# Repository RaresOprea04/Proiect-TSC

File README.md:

# InkTime - Open Source Smartwatch ⌚

InkTime este un start-up care își propune să creeze un smartwatch accesibil și complet open-source. Acest repository conține fișierele FINALE, inclusiv design-ul hardware (schematic + PCB 2D/3D în Fusion 360), fișierele de fabricație și documentația aferentă, cât și ceas-ul în forma sa finală, asamblat.

## 1. Diagrama Bloc a Sistemului

Diagrama de mai jos ilustrează arhitectura hardware a ceasului InkTime, având în centru procesorul nRF52840, înconjurat de modulele de power management, senzori și interfața cu utilizatorul.

```mermaid
flowchart LR
    %% Stiluri
    classDef power fill:#f9d0c4,stroke:#333,stroke-width:2px;
    classDef mcu fill:#d4e6f1,stroke:#333,stroke-width:2px;
    classDef peri fill:#d5f5e3,stroke:#333,stroke-width:2px;

    %% Power Block
    subgraph Power Management
        USB[Conector USB-C]:::power -->|VBUS 5V| BQ[BQ25180\nCharger Li-Po]:::power
        BAT[(Baterie Li-Po)]:::power <-->|VBAT| BQ
        BQ -->|VSYS| REG[RT6160\nRegulator 3.3V]:::power
    end

    %% MCU Block
    MCU{nRF52840 SoC\nMCU + Antenă BLE}:::mcu

    %% Peripherals
    subgraph Senzori & UI
        ACC[BMA421\nAccelerometru]:::peri
        BTN[Butoane Tactile]:::peri
    end

    subgraph Output
        EPD[Ecran E-Paper]:::peri
    end

    Debug[Interfață SWD\nProgramare]:::peri

    %% Power Connections (Linii groase)
    REG == 3.3V === MCU
    REG == 3.3V === ACC
    REG == 3.3V === EPD

    %% Data Connections (Linii normale)
    MCU <-->|I2C| ACC
    MCU -->|SPI| EPD
    BTN -->|GPIO| MCU
    MCU <-->|SWDIO / SWCLK| Debug
```

## 2. Bill of Materials (BOM)

Toate componentele pasive (rezistențe, condensatoare) sunt în format SMD 0201 sau 0402, conform specificațiilor proiectului. Mai jos sunt componentele integrate principale (IC-urile):

| Componentă / Modul | Rol | JLCPCB Part Link | Datasheet |
| :--- | :--- | :--- | :--- |
| **nRF52840-QIAA** | MCU principal (Bluetooth LE) | [Caută JLC](https://jlcpcb.com/parts) | [Datasheet nRF52840](https://infocenter.nordicsemi.com/pdf/nRF52840_PS_v1.1.pdf) |
| **BQ25180YBGR** | PMIC / LiPo Battery Charger | [Caută JLC](https://jlcpcb.com/parts) | [Datasheet BQ25180](https://www.ti.com/lit/ds/symlink/bq25180.pdf) |
| **RT6160AWSC** | DC/DC Buck-Boost Converter (3.3V) | [Caută JLC](https://jlcpcb.com/parts) | [Datasheet RT6160](https://www.richtek.com/assets/product_file/RT6160A/DS6160A-01.pdf) |
| **MAX17048G+T10** | Fuel Gauge (Monitorizare Baterie) | [Caută JLC](https://jlcpcb.com/parts) | [Datasheet MAX17048](https://datasheets.maximintegrated.com/en/ds/MAX17048-MAX17049.pdf) |
| **BMA421** | Senzor IMU (Accelerometru) | [Caută JLC](https://jlcpcb.com/parts) | [Datasheet BMA421](https://www.bosch-sensortec.com/media/boschsensortec/downloads/datasheets/bst-bma421-fl000.pdf) |
| **DRV2605YZFR** | Haptic Motor Driver | [Caută JLC](https://jlcpcb.com/parts) | [Datasheet DRV2605](https://www.ti.com/lit/ds/symlink/drv2605.pdf) |
| **E-Paper Display** | Conector Display FPC 24-pin | - | - |

---

## 3. Funcționalitate Hardware și Arhitectură

Sistemul este construit în jurul microcontroller-ului **Nordic nRF52840**, ales pentru eficiența energetică ridicată și capabilitățile native Bluetooth Low Energy (BLE). 

### Alimentare (Power Management)
* **Încărcare:** Sistemul folosește un încărcător liniar **BQ25180** compatibil cu baterii LiPo, alimentat prin mufa USB-C (5V). 
* **Regulare:** Deoarece bateria variază între 3.0V și 4.2V, folosim un convertor DC/DC Buck-Boost **RT6160** pentru a menține o tensiune stabilă de 3.3V necesară componentelor logice și display-ului.
* **Monitorizare:** Modulul **MAX17048** comunică prin I2C pentru a oferi SoC-ului informații exacte despre procentajul bateriei (State of Charge).

### Senzori și Interacțiune
* **Membru senzorial:** Un IMU **BMA421** comunică prin I2C cu microcontroller-ul. Folosește pini de interupt pentru a trezi procesorul (Wake-on-Motion), economisind astfel energie (ex: se aprinde display-ul doar când ridici mâna).
* **Display E-Paper:** Este controlat printr-o magistrală SPI (MISO, MOSI, SCK, CS) la care se adaugă semnalele de control specifice ecranelor cu cerneală electronică (BUSY, DC, RESET). Avantajul suprem este că ecranul reține imaginea fără a consuma energie (0mA consum static).
* **Feedback Haptic:** Un driver dedicat **DRV2605** este conectat pe magistrala I2C și controlează un motor de vibrații (shaker) pentru notificări.
* **Input Utilizator:** 3 butoane fizice cu rezistențe de pull-up hardware/software pentru navigarea în meniu.

### Estimări de consum energetic
* **Sleep Mode (System OFF):** ~1.5uA (nRF52840) + curenții de stand-by ai senzorilor = **< 5uA total**.
* **Display Refresh:** ~8mA timp de 1-2 secunde (doar la actualizarea orei).
* **BLE Tx/Rx Active:** ~5.3mA pe vârfuri scurte (câteva milisecunde).
Sistemul este extrem de eficient, asigurând o durată de viață a bateriei de câteva săptămâni, în funcție de frecvența refresh-urilor e-paper.

---

## 4. Maparea Pinilor nRF52840 (Pinout)

| Pin nRF52840 | Nume Semnal | Destinație | Rol / Explicație |
| :--- | :--- | :--- | :--- |
| `P0.06` | I2C_SDA | BMA421, BQ25180, MAX17048, DRV2605 | Linia de date pentru magistrala I2C comună. |
| `P0.07` | I2C_SCL | BMA421, BQ25180, MAX17048, DRV2605 | Linia de clock pentru magistrala I2C comună. |
| `P0.03` | SPI_MOSI | E-Paper Connector | Trimite comenzi și date de imagine către display. |
| `P0.02` | SPI_SCK | E-Paper Connector | Semnalul de clock pentru interfața SPI a display-ului. |
| `P0.05` | EPD_CS | E-Paper Connector | Chip Select (active low) pentru display-ul E-paper. |
| `P0.15` | EPD_DC | E-Paper Connector | Data/Command - indică dacă payload-ul trimis prin SPI este o comandă sau date de pixel. |
| `P0.17` | EPD_BUSY | E-Paper Connector | Citește starea de busy a display-ului pentru a ști când s-a terminat refresh-ul. |
| `P0.16` | EPD_RST | E-Paper Connector | Pinul de hardware reset pentru ecranul E-paper. |
| `P0.08` | IMU_INT1 | BMA421 | Wake-up interrupt (ex: trezirea sistemului la ridicarea mâinii). |
| `P1.04` | SW_UP | Buton Sus | Input navigație (activ low, folosind pull-up intern). |
| `P1.05` | SW_ENT | Buton Enter | Input navigație (activ low, folosind pull-up intern). |
| `P1.06` | SW_DN | Buton Jos | Input navigație (activ low, folosind pull-up intern). |

---

## 5. Design Log & Constrângeri pentru Review

### Imagini PCB și Asamblare 3D
*Aici puteți vedea design-ul plăcii de circuit și integrarea acesteia în carcasa printată.*

**Vedere PCB (Top & Bottom):**

**Integrare în Carcasă (Asamblare internă):**

### Jurnal de decizii (Design Log)
În timpul procesului de proiectare am respectat următoarele constrângeri și decizii de good-practice:
1. **Plane de Masă:** S-au implementat poligoane de GND atât pe layer-ul TOP cât și pe BOTTOM. S-a realizat Via Stitching abundent pentru a asigura un plan de referință solid, în special în apropierea modulului radio și a convertoarelor DC/DC.
2. **Zona Antenei:** Am respectat cu strictețe zona de clearance pentru antena integrată. S-a folosit un "Polygon Cutout" pe ambele straturi pentru a decupa cuprul complet de sub antenă, evitând astfel detunarea (detuning) acesteia și degradarea semnalului RF.
3. **Rutarea curentului:** Traseele de putere (VBUS, 3V3, VBAT) au fost rutate la o grosime optimizată de 0.3mm (unde spațiul a permis) pentru a minimiza căderea de tensiune, iar condensatoarele de decuplare (100nF) au fost amplasate strict, cât mai aproape de pinii de VDD ai integratelor.
4. **Acceptare Erori DRC:** Erorile de clearance și dimension rezultate din depășirea marginii plăcii de către componentele mecanice (mufa USB-C și butoanele fizice) au fost acceptate asumat, deoarece amplasarea lor este impusă de cotele carcasei exterioare.

---

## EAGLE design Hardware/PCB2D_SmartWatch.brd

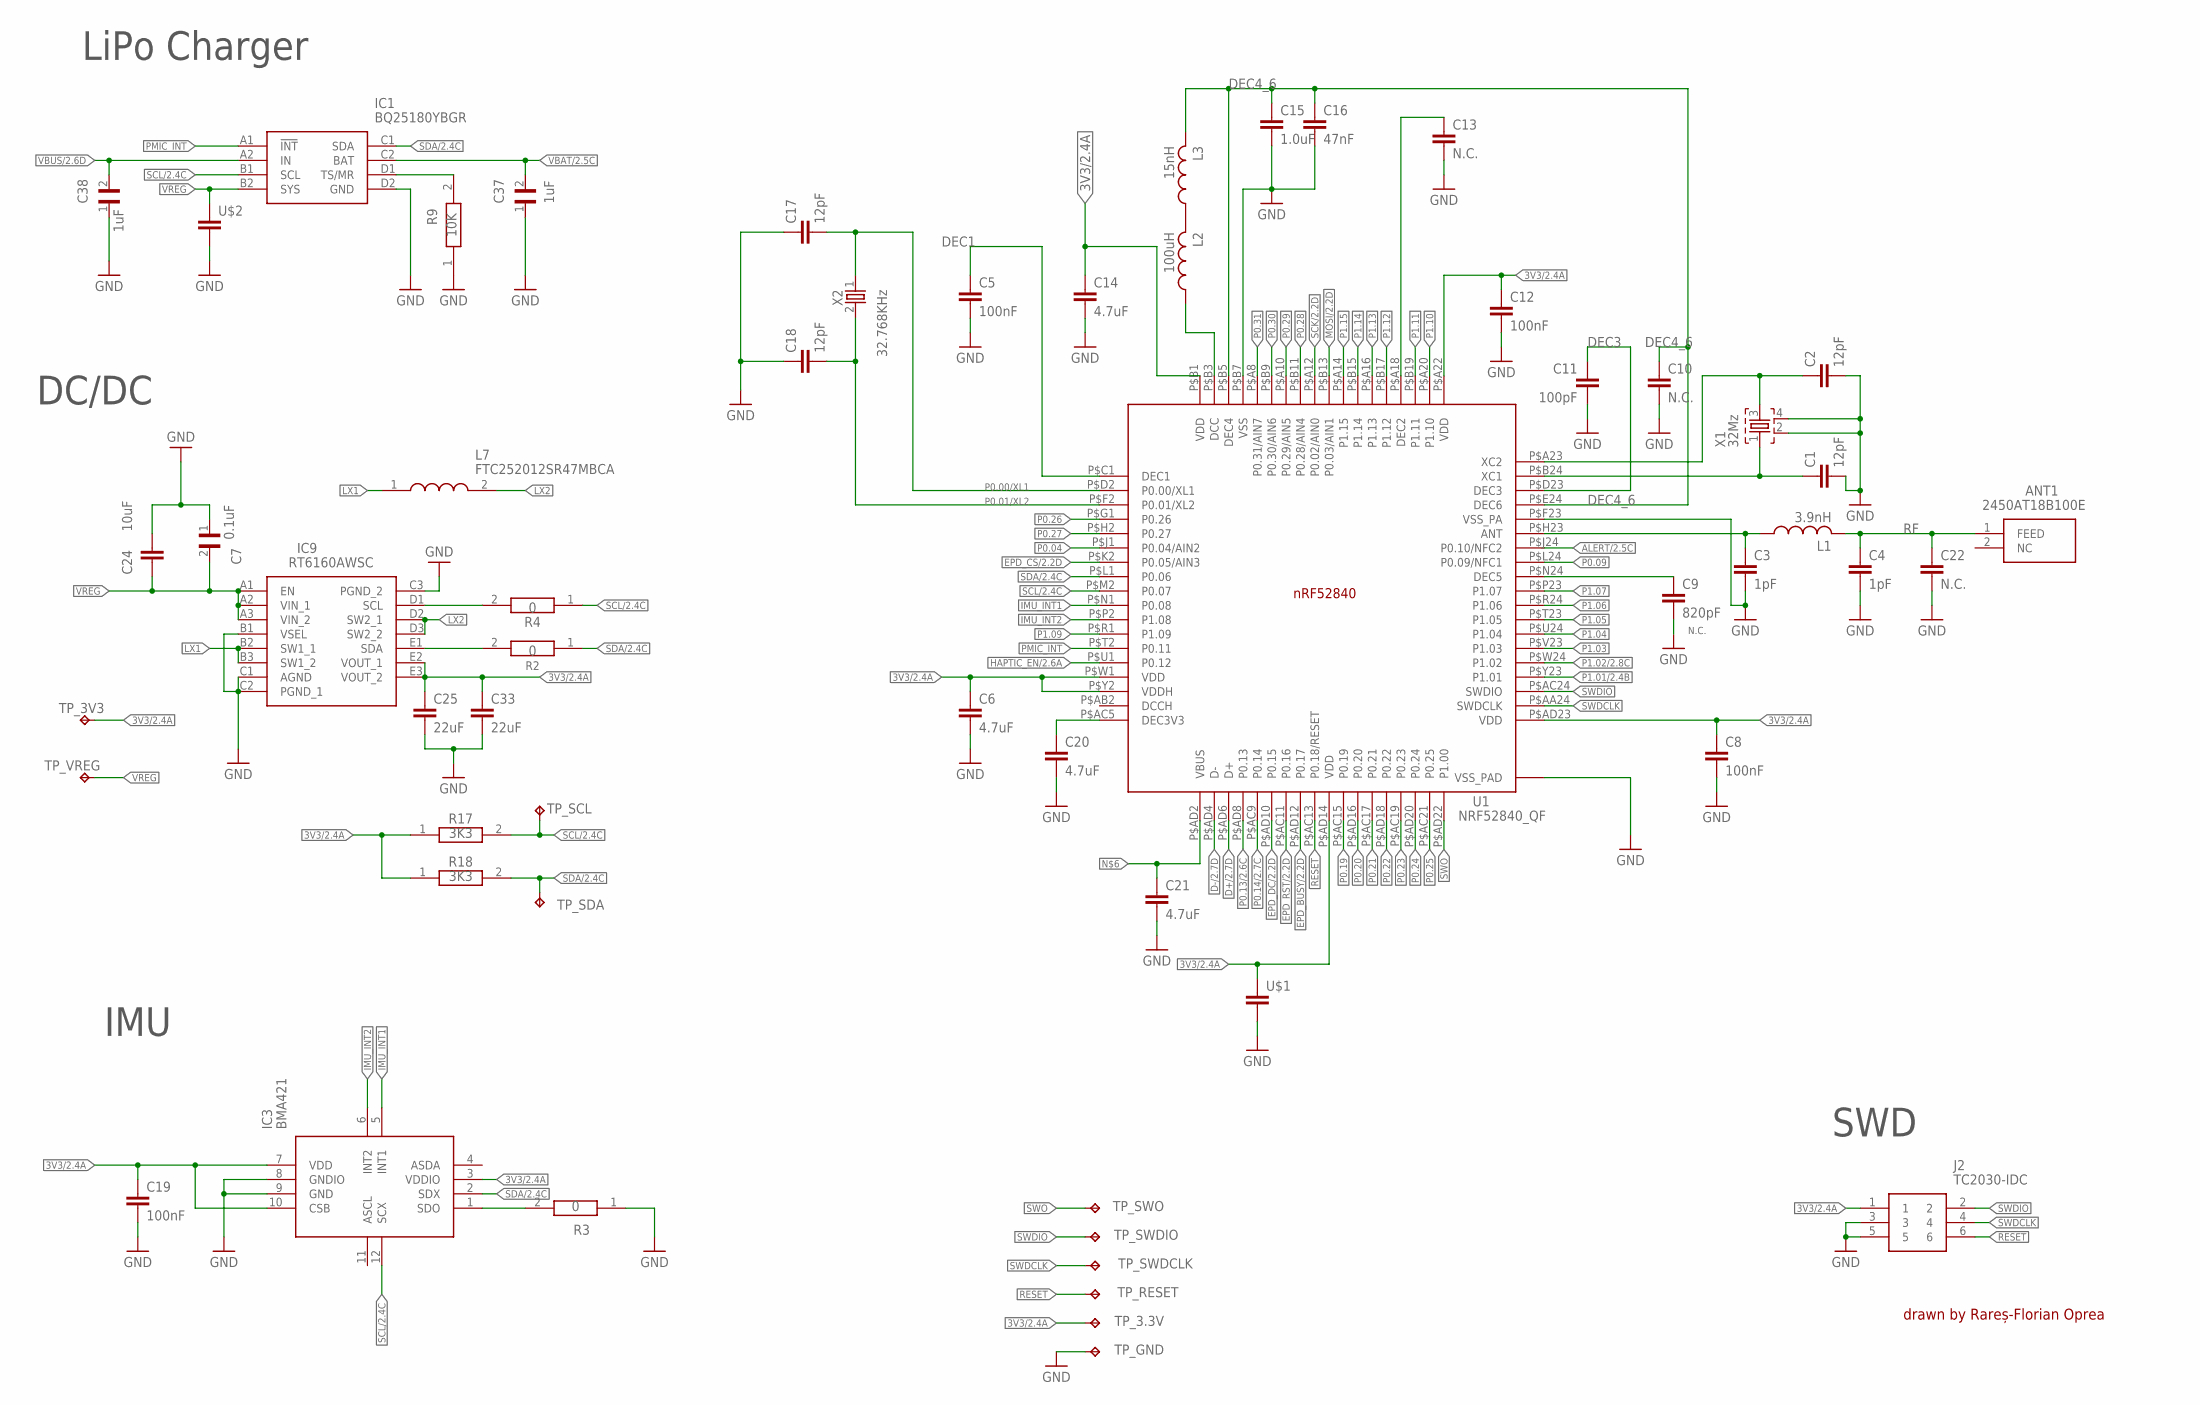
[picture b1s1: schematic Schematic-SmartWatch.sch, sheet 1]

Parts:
ANT1: 2450AT18B100E; 2450AT18B100E_ANTC3216X140N
C1, C2, C17, C18: 12pF; NORDIC_NRF_3_RESC0201_L
C3, C4: 1pF; NORDIC_NRF_3_RESC0201_L
C5, C8, C12, C19: 100nF; NORDIC_NRF_3_RESC0201_L
C6, C14, C20, C21: 4.7uF; NORDIC_NRF_3_RESC0201_L
C7: 0.1uF; GRM011R60J152KE01L_2_CAPC0201X13N
C9: 820pF; NORDIC_NRF_3_RESC0201_L
C10, C13, C22: N.C.; NORDIC_NRF_3_RESC0201_L
C11: 100pF; NORDIC_NRF_3_RESC0201_L
C15: 1.0uF; NORDIC_NRF_3_RESC0201_L
C16: 47nF; NORDIC_NRF_3_RESC0201_L
C24: 10uF; NORDIC_NRF_3_RESC0201_L
C25, C33: 22uF; NORDIC_NRF_3_RESC0201_L
C37: 1uF; GRM011R60J152KE01L_1_0201
C38: 1uF; GRM011R60J152KE01L_2_CAPC0201X13N
IC1: BQ25180YBGR; BQ25180YBGR_BGA8C40P2X4_100X155X50
IC3: BMA421; BMA423_BMA423
IC9: RT6160AWSC; RT6160AWSC_BGA15C40P3X5_140X230X60
J2: TC2030-IDC; TC2030-IDC_TC2030IDC
L1: 3.9nH; NORDIC_NRF_2_RESC0402_L
L2: 100uH; NORDIC_NRF_2_RESC0402_L
L3: 15nH; NORDIC_NRF_2_RESC0402_L
L7: FTC252012SR47MBCA; MLP2016SR47MT0S1_INDC2016X100N
R2, R4: 0; CPF0201D7K68C1_0201
R3: 0; ERA-1AEB3401C_0201
R9: 10K; ERA-1AEB3401C_0201
R17, R18: 3K3; CPF0201D7K68C1_0201
TP_3.3V, TP_3V3: HECTOR_WATCH_1_TPTP20R; HECTOR_WATCH_1_TP20R
TP_GND: HECTOR_WATCH_1_TPTP20R; HECTOR_WATCH_1_TP20R
TP_RESET: HECTOR_WATCH_1_TPTP20R; HECTOR_WATCH_1_TP20R
TP_SCL: HECTOR_WATCH_1_TPTP20R; HECTOR_WATCH_1_TP20R
TP_SDA: HECTOR_WATCH_1_TPTP20R; HECTOR_WATCH_1_TP20R
TP_SWDCLK: HECTOR_WATCH_1_TPTP20R; HECTOR_WATCH_1_TP20R
TP_SWDIO: HECTOR_WATCH_1_TPTP20R; HECTOR_WATCH_1_TP20R
TP_SWO: HECTOR_WATCH_1_TPTP20R; HECTOR_WATCH_1_TP20R
TP_VREG: HECTOR_WATCH_1_TPTP20R; HECTOR_WATCH_1_TP20R
U1: NRF52840_QF; NORDIC_NRF_4_AQFN50P700X700X85_HS-74N
U$1, U$2: NORDIC_NRF_3_CAPACITOR_0201_L; NORDIC_NRF_3_RESC0201_L
X1: 32Mz; NORDIC_NRF_BT-XTAL_2016_N
X2: 32.768KHz; NORDIC_NRF_1_XTAL_3215_N

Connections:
3V3/2.4A: C6.1, C8.1, C12.1, C14.1, C19.1, C25.1, C33.1, IC3.3 (VDDIO), IC3.7 (VDD), IC3.10 (CSB), IC9.E2 (VOUT_1), IC9.E3 (VOUT_2), J2.1, R17.1, R18.1, TP_3.3V.TP, TP_3V3.TP, U1.P$A22 (VDD), U1.P$AD14 (VDD), U1.P$AD23 (VDD), U1.P$B1 (VDD), U1.P$W1 (VDD), U1.P$Y2 (VDDH), U$1.1
ALERT/2.5C: U1.P$J24 (P0.10/NFC2)
D+/2.7D: U1.P$AD6 (D+)
D-/2.7D: U1.P$AD4 (D-)
DEC1: C5.1, U1.P$C1 (DEC1)
DEC3: C11.1, U1.P$D23 (DEC3)
DEC4_6: C10.1, C15.1, C16.1, L3.2, U1.P$B5 (DEC4), U1.P$E24 (DEC6)
EPD_BUSY/2.2D: U1.P$AD12 (P0.17)
EPD_CS/2.2D: U1.P$K2 (P0.05/AIN3)
EPD_DC/2.2D: U1.P$AD10 (P0.15)
EPD_RST/2.2D: U1.P$AC11 (P0.16)
GND: C1.2, C2.2, C3.2, C4.2, C5.2, C6.2, C7.1, C8.2, C10.2, C11.2, C12.2, C13.2, C14.2, C19.2, C20.2, C21.2, C22.2, C24.1, C37.1, C38.1, IC1.D2 (GND), IC3.8 (GNDIO), IC3.9 (GND), IC9.B1 (VSEL), IC9.C1 (AGND), IC9.C2 (PGND_1), J2.3, J2.5, R3.1, R9.1, TP_GND.TP, U1.P$74 (VSS_PAD), U1.P$75 (VSS_PAD), U1.P$76 (VSS_PAD), U1.P$77 (VSS_PAD), U1.P$78 (VSS_PAD), U1.P$79 (VSS_PAD), U1.P$80 (VSS_PAD), U1.P$81 (VSS_PAD), U1.P$82 (VSS_PAD), U1.P$83 (VSS_PAD), U1.P$84 (VSS_PAD), U1.P$85 (VSS_PAD), U1.P$86 (VSS_PAD), U1.P$87 (VSS_PAD), U1.P$88 (VSS_PAD), U1.P$89 (VSS_PAD), U1.P$90 (VSS_PAD), U1.P$F23 (VSS_PA), U$1.2, U$2.2, X1.2, X1.4; also elsewhere on the board
HAPTIC_EN/2.6A: U1.P$U1 (P0.12)
IMU_INT1: IC3.5 (INT1), U1.P$N1 (P0.08)
IMU_INT2: IC3.6 (INT2), U1.P$P2 (P1.08)
LX1: IC9.B2 (SW1_1), IC9.B3 (SW1_2), L7.1
LX2: IC9.D2 (SW2_1), IC9.D3 (SW2_2), L7.2
MOSI/2.2D: U1.P$B13 (P0.03/AIN1)
unnamed: L2.2, L3.1
unnamed: L2.1, U1.P$B3 (DCC)
unnamed: IC1.D1 (TS/MR), R9.2
unnamed: C15.2, C16.2, U1.P$B7 (VSS)
unnamed: C20.1, U1.P$AC5 (DEC3V3)
unnamed: C21.1, U1.P$AD2 (VBUS)
unnamed: C17.1, C18.1
unnamed: C3.1, L1.1, U1.P$H23 (ANT)
unnamed: C1.1, U1.P$B24 (XC1), X1.1
unnamed: C13.1, U1.P$A18 (DEC2)
unnamed: C9.1, U1.P$N24 (DEC5)
unnamed: C2.1, U1.P$A23 (XC2), X1.3
unnamed: IC3.1 (SDO), R3.2
unnamed: IC9.D1 (SCL), R4.2
unnamed: C25.2, C33.2
unnamed: IC9.E1 (SDA), R2.2
N.C.: C9.2
P0.00/XL1: C17.2, U1.P$D2 (P0.00/XL1), X2.1
P0.01/XL2: C18.2, U1.P$F2 (P0.01/XL2), X2.2
P0.04: U1.P$J1 (P0.04/AIN2)
P0.09: U1.P$L24 (P0.09/NFC1)
P0.13/2.6C: U1.P$AD8 (P0.13)
P0.14/2.7C: U1.P$AC9 (P0.14)
P0.19: U1.P$AC15 (P0.19)
P0.20: U1.P$AD16 (P0.20)
P0.21: U1.P$AC17 (P0.21)
P0.22: U1.P$AD18 (P0.22)
P0.23: U1.P$AC19 (P0.23)
P0.24: U1.P$AD20 (P0.24)
P0.25: U1.P$AC21 (P0.25)
P0.26: U1.P$G1 (P0.26)
P0.27: U1.P$H2 (P0.27)
P0.28: U1.P$B11 (P0.28/AIN4)
P0.29: U1.P$A10 (P0.29/AIN5)
P0.30: U1.P$B9 (P0.30/AIN6)
P0.31: U1.P$A8 (P0.31/AIN7)
P1.01/2.4B: U1.P$Y23 (P1.01)
P1.02/2.8C: U1.P$W24 (P1.02)
P1.03: U1.P$V23 (P1.03)
P1.04: U1.P$U24 (P1.04)
P1.05: U1.P$T23 (P1.05)
P1.06: U1.P$R24 (P1.06)
P1.07: U1.P$P23 (P1.07)
P1.09: U1.P$R1 (P1.09)
P1.10: U1.P$A20 (P1.10)
P1.11: U1.P$B19 (P1.11)
P1.12: U1.P$B17 (P1.12)
P1.13: U1.P$A16 (P1.13)
P1.14: U1.P$B15 (P1.14)
P1.15: U1.P$A14 (P1.15)
PMIC_INT: IC1.A1 (!INT), U1.P$T2 (P0.11)
RESET: J2.6, TP_RESET.TP, U1.P$AC13 (P0.18/RESET)
RF: ANT1.1 (FEED), C4.1, C22.1, L1.2
SCK/2.2D: U1.P$A12 (P0.02/AIN0)
SCL/2.4C: IC1.B1 (SCL), IC3.12 (SCX), R4.1, R17.2, TP_SCL.TP, U1.P$M2 (P0.07)
SDA/2.4C: IC1.C1 (SDA), IC3.2 (SDX), R2.1, R18.2, TP_SDA.TP, U1.P$L1 (P0.06)
SWDCLK: J2.4, TP_SWDCLK.TP, U1.P$AA24 (SWDCLK)
SWDIO: J2.2, TP_SWDIO.TP, U1.P$AC24 (SWDIO)
SWO: TP_SWO.TP, U1.P$AD22 (P1.00)
VBAT/2.5C: C37.2, IC1.C2 (BAT)
VBUS/2.6D: C38.2, IC1.A2 (IN)
VREG: C7.2, C24.2, IC1.B2 (SYS), IC9.A1 (EN), IC9.A2 (VIN_1), IC9.A3 (VIN_2), TP_VREG.TP, U$2.1

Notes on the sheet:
LiPo Charger
IMU
DC/DC
SWD
drawn by Rareș-Florian Oprea

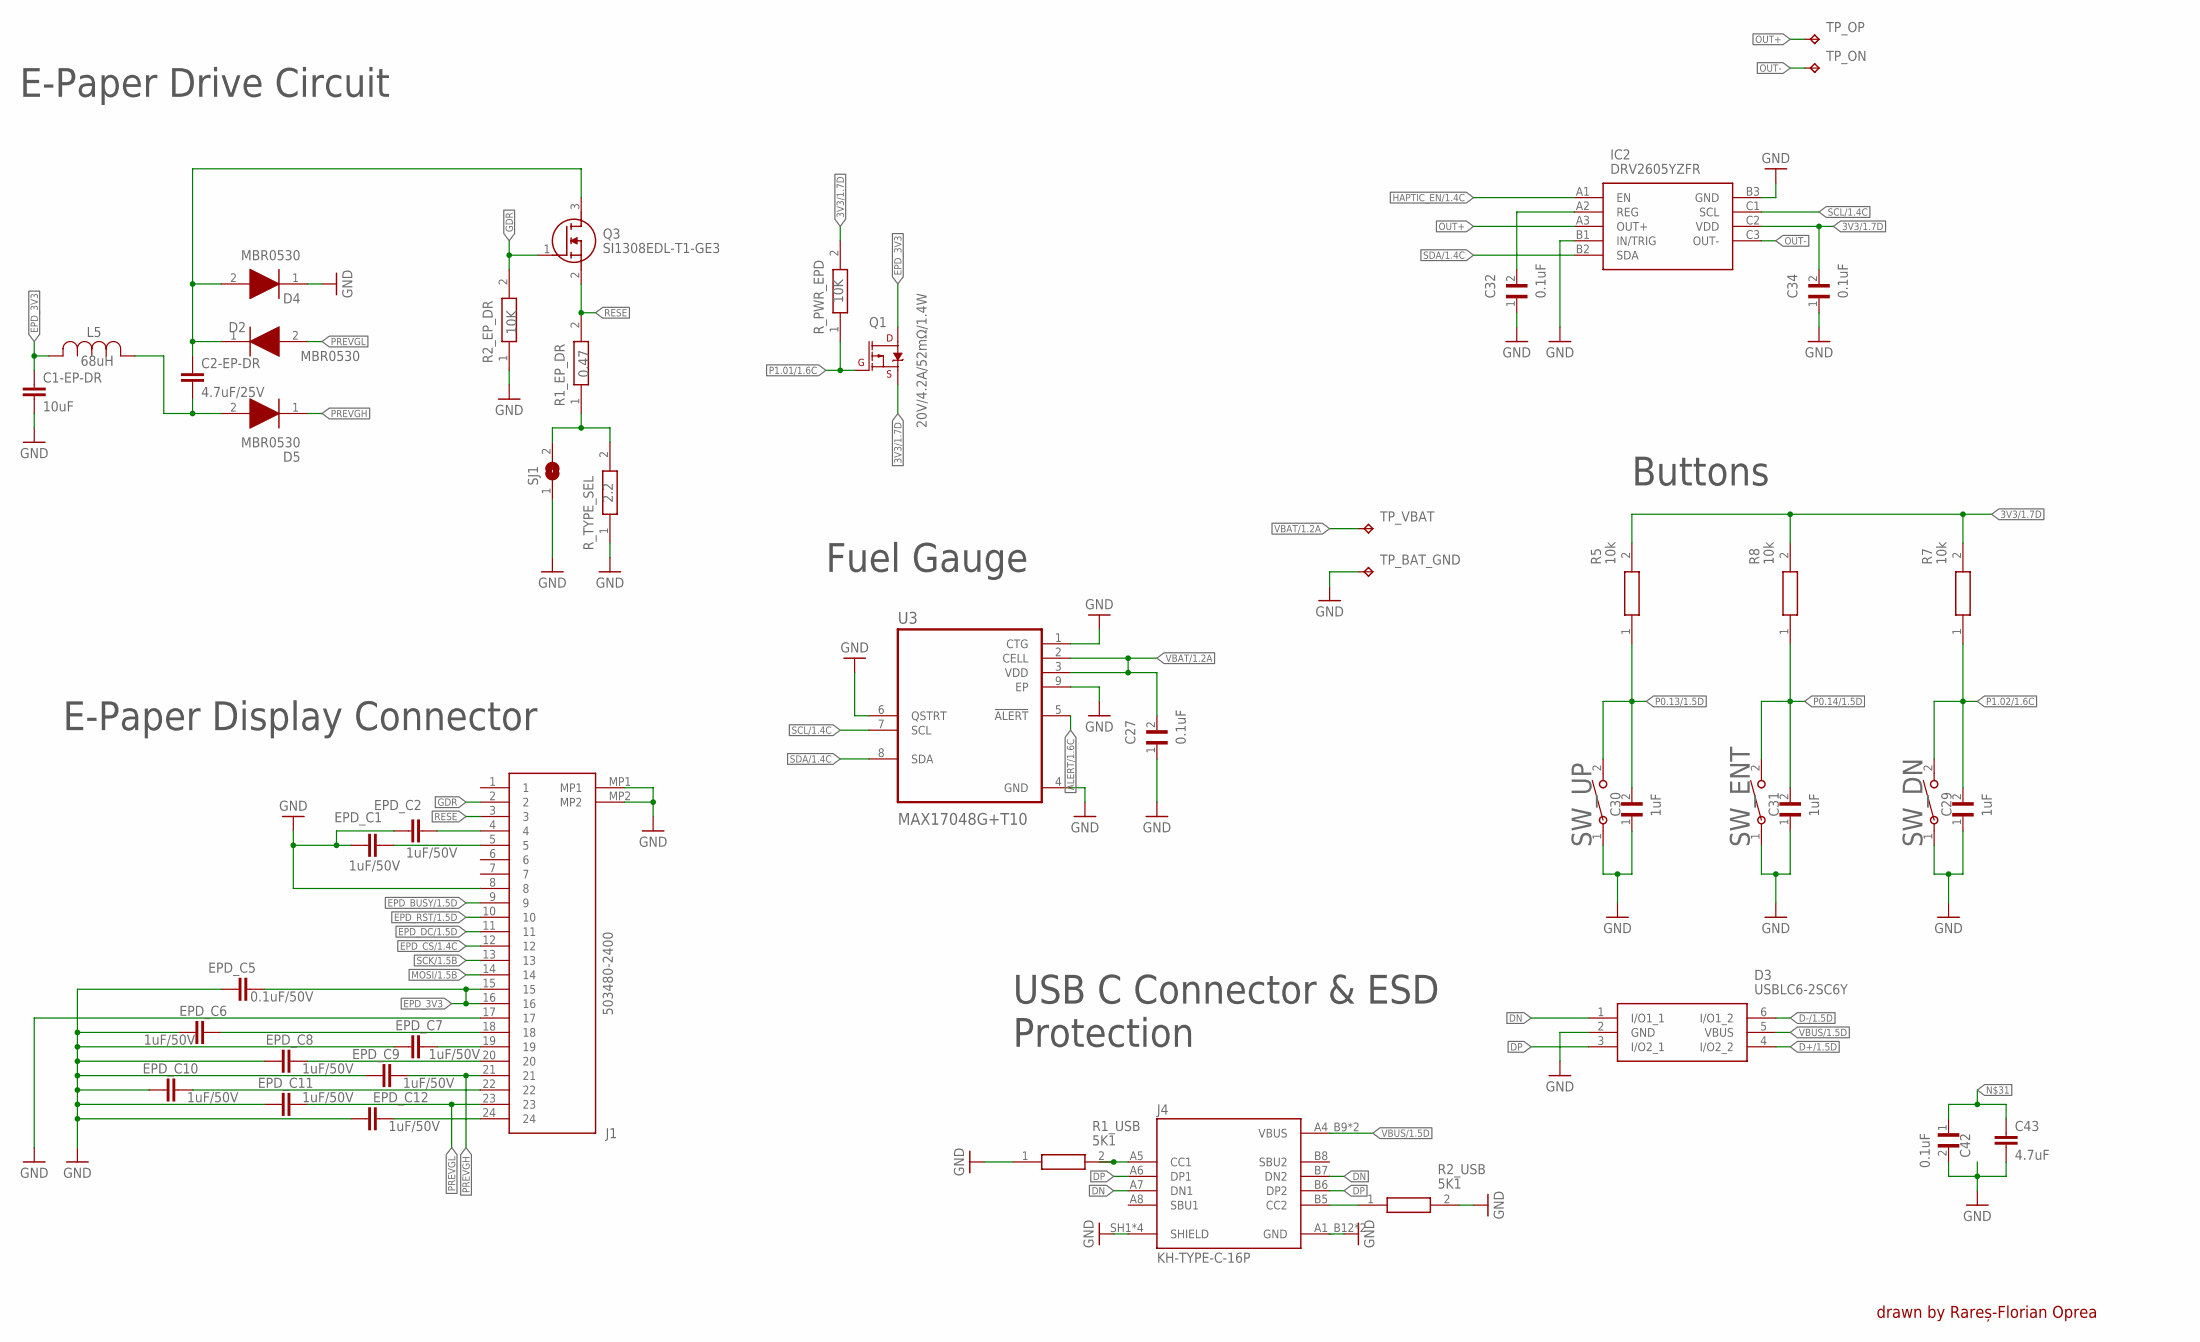
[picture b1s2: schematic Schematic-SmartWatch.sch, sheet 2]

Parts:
C1-EP-DR: 10uF; ESP32_C6_LIBRARY_1_ESP32_WROVER_EAGLE-LTSPICE_C0402
C2-EP-DR: 4.7uF/25V; ESP32_C6_LIBRARY_1_ESP32_WROVER_EAGLE-LTSPICE_C0402
C27, C32, C34: 0.1uF; GRM011R60J152KE01L_2_CAPC0201X13N
C29, C30, C31: 1uF; GRM011R60J152KE01L_2_CAPC0201X13N
C42: 0.1uF; GRM011R60J152KE01L_1_0201
C43: 4.7uF; ESP32_C6_LIBRARY_1_ESP32_WROVER_EAGLE-LTSPICE_C0402
D2, D4, D5: MBR0530; ESP32_C6_LIBRARY_5_SOD3716X135N
D3: USBLC6-2SC6Y; ESP32_C6_LIBRARY_3_SOT95P280X145-6N
EPD_C1, EPD_C2, EPD_C6, EPD_C7, EPD_C8, EPD_C9, EPD_C10, EPD_C11, EPD_C12: 1uF/50V; NORDIC_NRF_3_RESC0201_L
EPD_C5: 0.1uF/50V; NORDIC_NRF_3_RESC0201_L
IC2: DRV2605YZFR; DRV2605YZFR_BGA9C50P3X3_144X144X62
J1: 503480-2400; 503480-2400_5034802400
J4: KH-TYPE-C-16P; KH-TYPE-C-16P_KINGHELM_KH-TYPE-C-16P
L5: 68uH; ESP32_C6_LIBRARY_2_IND_4828-WE-TPC_WRE
Q1: 20V/4.2A/52mΩ/1.4W; ESP32_C6_LIBRARY_4_ESP32_C6_LIBRARY_4_ESP32_C6_LIBRARY_4_ES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
Q3: SI1308EDL-T1-GE3; ESP32_C6_LIBRARY_6_SOT65P210X110-3N
R1_EP_DR: 0.47; ERA-1AEB3401C_0201
R1_USB, R2_USB: 5K1; ERA-1AEB3401C_0201
R2_EP_DR: 10K; ERA-1AEB3401C_0201
R5, R7, R8: 10k; ERA-1AEB3401C_0201
R_PWR_EPD: 10K; ERA-1AEB3401C_0201
R_TYPE_SEL: 2.2; ERA-1AEB3401C_0201
SJ1: ESP32_C6_LIBRARY_7_JUMPER_SJ
SW_DN: 2025-10-22_07-23-44_LIBRARY_EVP-AKE31ASW_EVP-AKE3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; 2025-10-22_07-23-44_LIBRARY_SW_EVP-AKE31A_PAN
SW_ENT: 2025-10-22_07-23-44_LIBRARY_EVP-AKE31ASW_EVP-AKE3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; 2025-10-22_07-23-44_LIBRARY_SW_EVP-AKE31A_PAN
SW_UP: 2025-10-22_07-23-44_LIBRARY_EVP-AKE31ASW_EVP-AKE3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; 2025-10-22_07-23-44_LIBRARY_SW_EVP-AKE31A_PAN
TP_BAT_GND: HECTOR_WATCH_1_TPTP20R; HECTOR_WATCH_1_TP20R
TP_ON: HECTOR_WATCH_1_TPTP20R; HECTOR_WATCH_1_TP20R
TP_OP: HECTOR_WATCH_1_TPTP20R; HECTOR_WATCH_1_TP20R
TP_VBAT: HECTOR_WATCH_1_TPTP20R; HECTOR_WATCH_1_TP20R
U3: MAX17048G+T10; ESP32_C6_LIBRARY_SON50P200X200X80-9N

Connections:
3V3/1.7D: C34.2, IC2.C2 (VDD), Q1.2 (S), R5.2, R7.2, R8.2, R_PWR_EPD.2
ALERT/1.6C: U3.5 (!ALERT)
D+/1.5D: D3.4 (I/O2_2)
D-/1.5D: D3.6 (I/O1_2)
DN: D3.1 (I/O1_1), J4.A7 (DN1), J4.B7 (DN2)
DP: D3.3 (I/O2_1), J4.A6 (DP1), J4.B6 (DP2)
EPD_3V3: C1-EP-DR.1, EPD_C5.2, J1.15, J1.16, L5.2, Q1.3 (D)
EPD_BUSY/1.5D: J1.9
EPD_CS/1.4C: J1.12
EPD_DC/1.5D: J1.11
EPD_RST/1.5D: J1.10
GDR: J1.2, Q3.1 (G), R2_EP_DR.2
GND: C1-EP-DR.2, C27.1, C29.1, C30.1, C31.1, C32.1, C34.1, C42.2, C43.2, D4.1 (K), EPD_C1.1, EPD_C2.1, EPD_C5.1, EPD_C6.1, EPD_C7.1, EPD_C8.1, EPD_C9.1, EPD_C10.1, EPD_C11.1, EPD_C12.1, IC2.B1 (IN/TRIG), J1.8, J1.17, J1.MP1, J1.MP2, J4.A1_B12 (GND), J4.A12_B1 (GND), J4.SH1 (SHIELD), J4.SH2 (SHIELD), J4.SH3 (SHIELD), J4.SH4 (SHIELD), R1_USB.1, R2_EP_DR.1, R2_USB.2, R_TYPE_SEL.1, SJ1.1, SW_DN.1, SW_ENT.1, SW_UP.1, TP_BAT_GND.TP, U3.1 (CTG), U3.4 (GND), U3.6 (QSTRT), U3.9 (EP); also elsewhere on the board
HAPTIC_EN/1.4C: IC2.A1 (EN)
MOSI/1.5B: J1.14
unnamed: EPD_C2.2, J1.4
unnamed: EPD_C1.2, J1.5
unnamed: EPD_C12.2, J1.24
unnamed: R1_EP_DR.1, R_TYPE_SEL.2, SJ1.2
unnamed: C2-EP-DR.2, D5.2 (A), L5.1
unnamed: EPD_C10.2, J1.22
unnamed: C2-EP-DR.1, D2.1 (K), D4.2 (A), Q3.3 (D)
unnamed: EPD_C7.2, J1.19
unnamed: EPD_C8.2, J1.20
unnamed: EPD_C6.2, J1.18
unnamed: C32.2, IC2.A2 (REG)
unnamed: C42.1, C43.1
unnamed: J4.B5 (CC2), R2_USB.1
unnamed: J4.A5 (CC1), R1_USB.2
OUT+: IC2.A3 (OUT+), TP_OP.TP
OUT-: IC2.C3 (OUT-), TP_ON.TP
P0.13/1.5D: C30.2, R5.1, SW_UP.2
P0.14/1.5D: C31.2, R8.1, SW_ENT.2
P1.01/1.6C: Q1.1 (G), R_PWR_EPD.1
P1.02/1.6C: C29.2, R7.1, SW_DN.2
PREVGH: D5.1 (K), EPD_C9.2, J1.21
PREVGL: D2.2 (A), EPD_C11.2, J1.23
RESE: J1.3, Q3.2 (S), R1_EP_DR.2
SCK/1.5B: J1.13
SCL/1.4C: IC2.C1 (SCL), U3.7 (SCL)
SDA/1.4C: IC2.B2 (SDA), U3.8 (SDA)
VBAT/1.2A: C27.2, TP_VBAT.TP, U3.2 (CELL), U3.3 (VDD)
VBUS/1.5D: D3.5 (VBUS), J4.A4_B9 (VBUS), J4.A9_B4 (VBUS)

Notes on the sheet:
drawn by Rareș-Florian Oprea
E-Paper Display Connector
E-Paper Drive Circuit
Fuel Gauge
Buttons
USB C Connector & ESD Protection

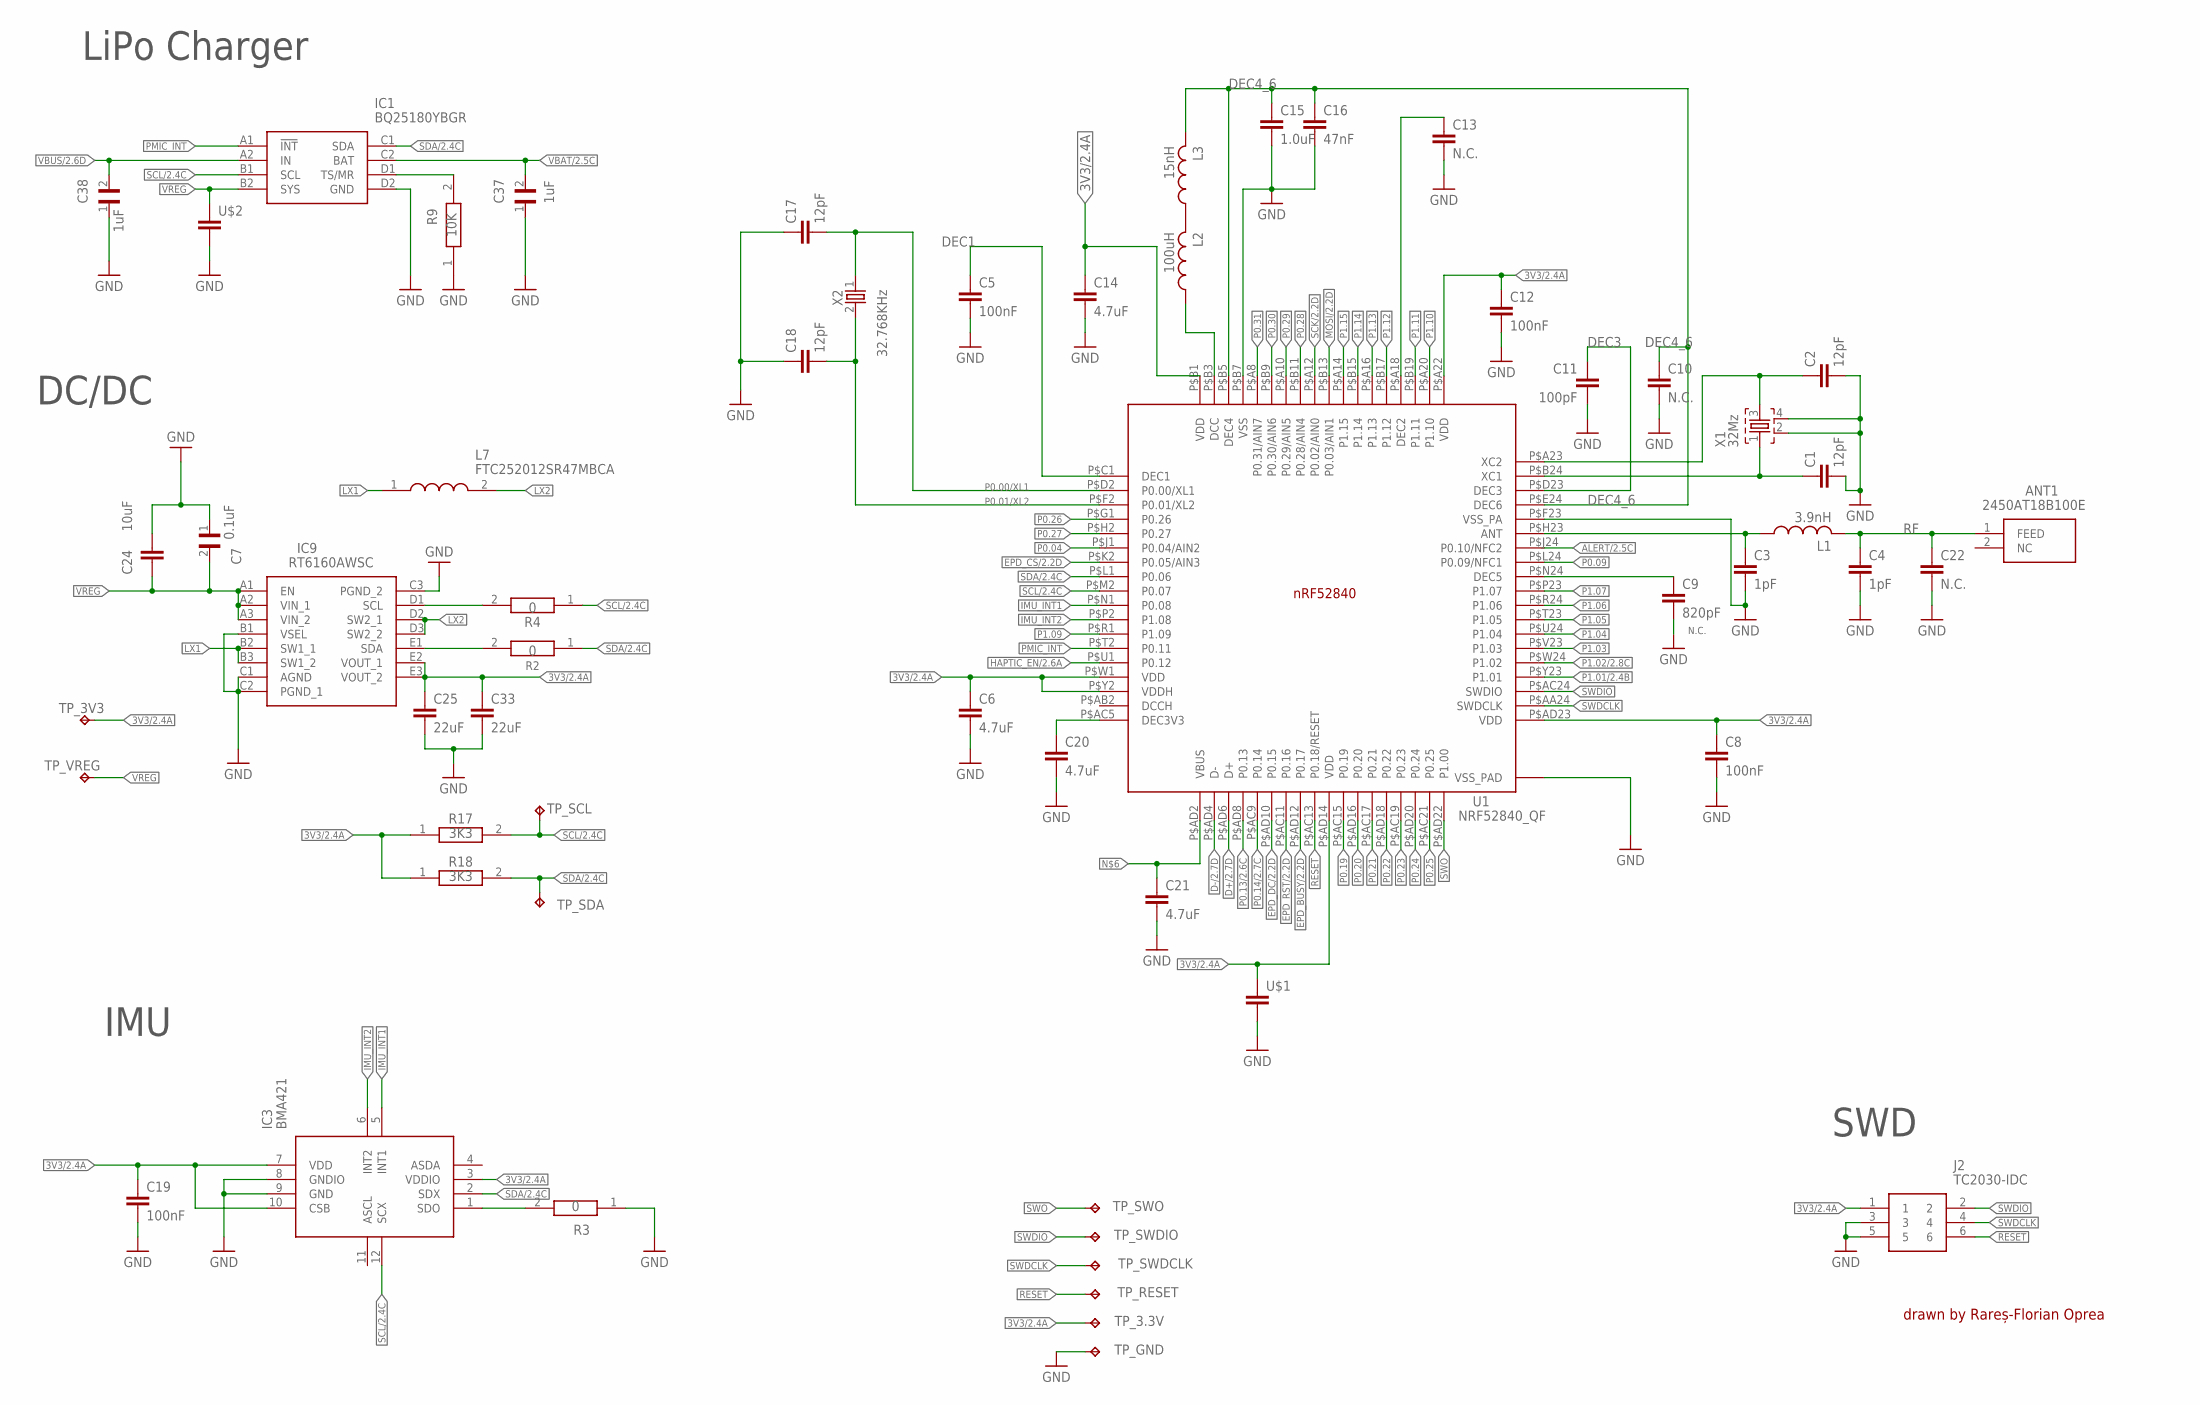
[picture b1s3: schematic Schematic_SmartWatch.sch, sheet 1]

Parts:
ANT1: 2450AT18B100E; 2450AT18B100E_ANTC3216X140N
C1, C2, C17, C18: 12pF; NORDIC_NRF_3_RESC0201_L
C3, C4: 1pF; NORDIC_NRF_3_RESC0201_L
C5, C8, C12, C19: 100nF; NORDIC_NRF_3_RESC0201_L
C6, C14, C20, C21: 4.7uF; NORDIC_NRF_3_RESC0201_L
C7: 0.1uF; GRM011R60J152KE01L_2_CAPC0201X13N
C9: 820pF; NORDIC_NRF_3_RESC0201_L
C10, C13, C22: N.C.; NORDIC_NRF_3_RESC0201_L
C11: 100pF; NORDIC_NRF_3_RESC0201_L
C15: 1.0uF; NORDIC_NRF_3_RESC0201_L
C16: 47nF; NORDIC_NRF_3_RESC0201_L
C24: 10uF; NORDIC_NRF_3_RESC0201_L
C25, C33: 22uF; NORDIC_NRF_3_RESC0201_L
C37: 1uF; GRM011R60J152KE01L_1_0201
C38: 1uF; GRM011R60J152KE01L_2_CAPC0201X13N
IC1: BQ25180YBGR; BQ25180YBGR_BGA8C40P2X4_100X155X50
IC3: BMA421; BMA423_BMA423
IC9: RT6160AWSC; RT6160AWSC_BGA15C40P3X5_140X230X60
J2: TC2030-IDC; TC2030-IDC_TC2030IDC
L1: 3.9nH; NORDIC_NRF_2_RESC0402_L
L2: 100uH; NORDIC_NRF_2_RESC0402_L
L3: 15nH; NORDIC_NRF_2_RESC0402_L
L7: FTC252012SR47MBCA; MLP2016SR47MT0S1_INDC2016X100N
R2, R4: 0; CPF0201D7K68C1_0201
R3: 0; ERA-1AEB3401C_0201
R9: 10K; ERA-1AEB3401C_0201
R17, R18: 3K3; CPF0201D7K68C1_0201
TP_3.3V, TP_3V3: HECTOR_WATCH_1_TPTP20R; HECTOR_WATCH_1_TP20R
TP_GND: HECTOR_WATCH_1_TPTP20R; HECTOR_WATCH_1_TP20R
TP_RESET: HECTOR_WATCH_1_TPTP20R; HECTOR_WATCH_1_TP20R
TP_SCL: HECTOR_WATCH_1_TPTP20R; HECTOR_WATCH_1_TP20R
TP_SDA: HECTOR_WATCH_1_TPTP20R; HECTOR_WATCH_1_TP20R
TP_SWDCLK: HECTOR_WATCH_1_TPTP20R; HECTOR_WATCH_1_TP20R
TP_SWDIO: HECTOR_WATCH_1_TPTP20R; HECTOR_WATCH_1_TP20R
TP_SWO: HECTOR_WATCH_1_TPTP20R; HECTOR_WATCH_1_TP20R
TP_VREG: HECTOR_WATCH_1_TPTP20R; HECTOR_WATCH_1_TP20R
U1: NRF52840_QF; NORDIC_NRF_4_AQFN50P700X700X85_HS-74N
U$1, U$2: NORDIC_NRF_3_CAPACITOR_0201_L; NORDIC_NRF_3_RESC0201_L
X1: 32Mz; NORDIC_NRF_BT-XTAL_2016_N
X2: 32.768KHz; NORDIC_NRF_1_XTAL_3215_N

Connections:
3V3/2.4A: C6.1, C8.1, C12.1, C14.1, C19.1, C25.1, C33.1, IC3.3 (VDDIO), IC3.7 (VDD), IC3.10 (CSB), IC9.E2 (VOUT_1), IC9.E3 (VOUT_2), J2.1, R17.1, R18.1, TP_3.3V.TP, TP_3V3.TP, U1.P$A22 (VDD), U1.P$AD14 (VDD), U1.P$AD23 (VDD), U1.P$B1 (VDD), U1.P$W1 (VDD), U1.P$Y2 (VDDH), U$1.1
ALERT/2.5C: U1.P$J24 (P0.10/NFC2)
D+/2.7D: U1.P$AD6 (D+)
D-/2.7D: U1.P$AD4 (D-)
DEC1: C5.1, U1.P$C1 (DEC1)
DEC3: C11.1, U1.P$D23 (DEC3)
DEC4_6: C10.1, C15.1, C16.1, L3.2, U1.P$B5 (DEC4), U1.P$E24 (DEC6)
EPD_BUSY/2.2D: U1.P$AD12 (P0.17)
EPD_CS/2.2D: U1.P$K2 (P0.05/AIN3)
EPD_DC/2.2D: U1.P$AD10 (P0.15)
EPD_RST/2.2D: U1.P$AC11 (P0.16)
GND: C1.2, C2.2, C3.2, C4.2, C5.2, C6.2, C7.1, C8.2, C10.2, C11.2, C12.2, C13.2, C14.2, C19.2, C20.2, C21.2, C22.2, C24.1, C37.1, C38.1, IC1.D2 (GND), IC3.8 (GNDIO), IC3.9 (GND), IC9.B1 (VSEL), IC9.C1 (AGND), IC9.C2 (PGND_1), J2.3, J2.5, R3.1, R9.1, TP_GND.TP, U1.P$74 (VSS_PAD), U1.P$75 (VSS_PAD), U1.P$76 (VSS_PAD), U1.P$77 (VSS_PAD), U1.P$78 (VSS_PAD), U1.P$79 (VSS_PAD), U1.P$80 (VSS_PAD), U1.P$81 (VSS_PAD), U1.P$82 (VSS_PAD), U1.P$83 (VSS_PAD), U1.P$84 (VSS_PAD), U1.P$85 (VSS_PAD), U1.P$86 (VSS_PAD), U1.P$87 (VSS_PAD), U1.P$88 (VSS_PAD), U1.P$89 (VSS_PAD), U1.P$90 (VSS_PAD), U1.P$F23 (VSS_PA), U$1.2, U$2.2, X1.2, X1.4; also elsewhere on the board
HAPTIC_EN/2.6A: U1.P$U1 (P0.12)
IMU_INT1: IC3.5 (INT1), U1.P$N1 (P0.08)
IMU_INT2: IC3.6 (INT2), U1.P$P2 (P1.08)
LX1: IC9.B2 (SW1_1), IC9.B3 (SW1_2), L7.1
LX2: IC9.D2 (SW2_1), IC9.D3 (SW2_2), L7.2
MOSI/2.2D: U1.P$B13 (P0.03/AIN1)
unnamed: L2.2, L3.1
unnamed: L2.1, U1.P$B3 (DCC)
unnamed: IC1.D1 (TS/MR), R9.2
unnamed: C15.2, C16.2, U1.P$B7 (VSS)
unnamed: C20.1, U1.P$AC5 (DEC3V3)
unnamed: C21.1, U1.P$AD2 (VBUS)
unnamed: C17.1, C18.1
unnamed: C3.1, L1.1, U1.P$H23 (ANT)
unnamed: C1.1, U1.P$B24 (XC1), X1.1
unnamed: C13.1, U1.P$A18 (DEC2)
unnamed: C9.1, U1.P$N24 (DEC5)
unnamed: C2.1, U1.P$A23 (XC2), X1.3
unnamed: IC3.1 (SDO), R3.2
unnamed: IC9.D1 (SCL), R4.2
unnamed: C25.2, C33.2
unnamed: IC9.E1 (SDA), R2.2
N.C.: C9.2
P0.00/XL1: C17.2, U1.P$D2 (P0.00/XL1), X2.1
P0.01/XL2: C18.2, U1.P$F2 (P0.01/XL2), X2.2
P0.04: U1.P$J1 (P0.04/AIN2)
P0.09: U1.P$L24 (P0.09/NFC1)
P0.13/2.6C: U1.P$AD8 (P0.13)
P0.14/2.7C: U1.P$AC9 (P0.14)
P0.19: U1.P$AC15 (P0.19)
P0.20: U1.P$AD16 (P0.20)
P0.21: U1.P$AC17 (P0.21)
P0.22: U1.P$AD18 (P0.22)
P0.23: U1.P$AC19 (P0.23)
P0.24: U1.P$AD20 (P0.24)
P0.25: U1.P$AC21 (P0.25)
P0.26: U1.P$G1 (P0.26)
P0.27: U1.P$H2 (P0.27)
P0.28: U1.P$B11 (P0.28/AIN4)
P0.29: U1.P$A10 (P0.29/AIN5)
P0.30: U1.P$B9 (P0.30/AIN6)
P0.31: U1.P$A8 (P0.31/AIN7)
P1.01/2.4B: U1.P$Y23 (P1.01)
P1.02/2.8C: U1.P$W24 (P1.02)
P1.03: U1.P$V23 (P1.03)
P1.04: U1.P$U24 (P1.04)
P1.05: U1.P$T23 (P1.05)
P1.06: U1.P$R24 (P1.06)
P1.07: U1.P$P23 (P1.07)
P1.09: U1.P$R1 (P1.09)
P1.10: U1.P$A20 (P1.10)
P1.11: U1.P$B19 (P1.11)
P1.12: U1.P$B17 (P1.12)
P1.13: U1.P$A16 (P1.13)
P1.14: U1.P$B15 (P1.14)
P1.15: U1.P$A14 (P1.15)
PMIC_INT: IC1.A1 (!INT), U1.P$T2 (P0.11)
RESET: J2.6, TP_RESET.TP, U1.P$AC13 (P0.18/RESET)
RF: ANT1.1 (FEED), C4.1, C22.1, L1.2
SCK/2.2D: U1.P$A12 (P0.02/AIN0)
SCL/2.4C: IC1.B1 (SCL), IC3.12 (SCX), R4.1, R17.2, TP_SCL.TP, U1.P$M2 (P0.07)
SDA/2.4C: IC1.C1 (SDA), IC3.2 (SDX), R2.1, R18.2, TP_SDA.TP, U1.P$L1 (P0.06)
SWDCLK: J2.4, TP_SWDCLK.TP, U1.P$AA24 (SWDCLK)
SWDIO: J2.2, TP_SWDIO.TP, U1.P$AC24 (SWDIO)
SWO: TP_SWO.TP, U1.P$AD22 (P1.00)
VBAT/2.5C: C37.2, IC1.C2 (BAT)
VBUS/2.6D: C38.2, IC1.A2 (IN)
VREG: C7.2, C24.2, IC1.B2 (SYS), IC9.A1 (EN), IC9.A2 (VIN_1), IC9.A3 (VIN_2), TP_VREG.TP, U$2.1

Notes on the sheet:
LiPo Charger
IMU
DC/DC
SWD
drawn by Rareș-Florian Oprea

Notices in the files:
parts and their libraries:
COPYRIGHT: Copyright (C) 2024 Ultra Librarian. All rights reserved.
COPYRIGHT: Copyright (C) 2025 Ultra Librarian. All rights reserved.
